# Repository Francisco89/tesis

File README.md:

tesis
=====

El repositorio de mi tesis.

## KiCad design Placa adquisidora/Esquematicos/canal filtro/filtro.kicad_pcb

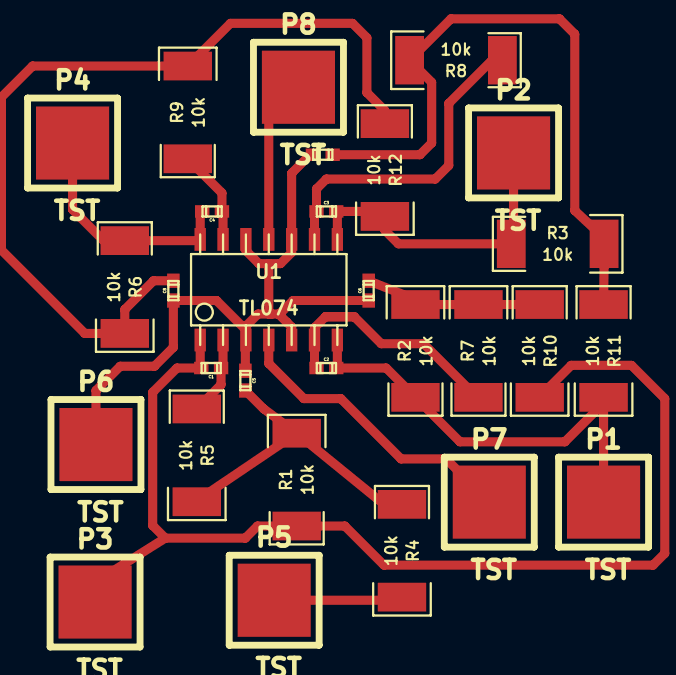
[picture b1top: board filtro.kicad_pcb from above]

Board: 2 copper layers, 29 parts (0 on the bottom side), 16 nets.

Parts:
C1: 412pF; c_0402
C2: 357pF; c_0402
C3: 237pF; c_0402
C4: 82.5pF; c_0402
C5: 976pF; c_0402
C6: 1.15nF; c_0402
C7: 1.74nF; c_0402
C8: 4.87nF; c_0402
P1, P2, P3, P4, P5, P6, P7, P8: TST; 1PIN_SMD
R1, R2, R3, R4, R5, R6, R7, R8, R9, R10, R11, R12: 10k; r_2010
U1: TL074; so-14

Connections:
AGND: C5.2, C6.2, C7.2, C8.2, P6.1, U1.3, U1.5, U1.10, U1.12
unnamed: C1.2, R5.2, U1.2
unnamed: C2.2, R7.2, U1.6
unnamed: C3.1, P2.1, R3.2, R12.1, U1.8
unnamed: C4.2, R9.2, U1.13
unnamed: C1.1, P3.1, R1.2, R10.1, U1.1
unnamed: C2.1, P1.1, R2.2, R11.1, U1.7
unnamed: C3.2, R8.2, U1.9
unnamed: C7.1, R3.1, R8.1, R11.2
unnamed: C8.1, R6.1, R9.1, R12.2
unnamed: C5.1, R1.1, R4.2, R5.1
unnamed: C6.1, R2.1, R7.1, R10.2
unnamed: P5.1, R4.1
unnamed: C4.1, P4.1, R6.2, U1.14
VCC: P7.1, U1.4
VSS: P8.1, U1.11

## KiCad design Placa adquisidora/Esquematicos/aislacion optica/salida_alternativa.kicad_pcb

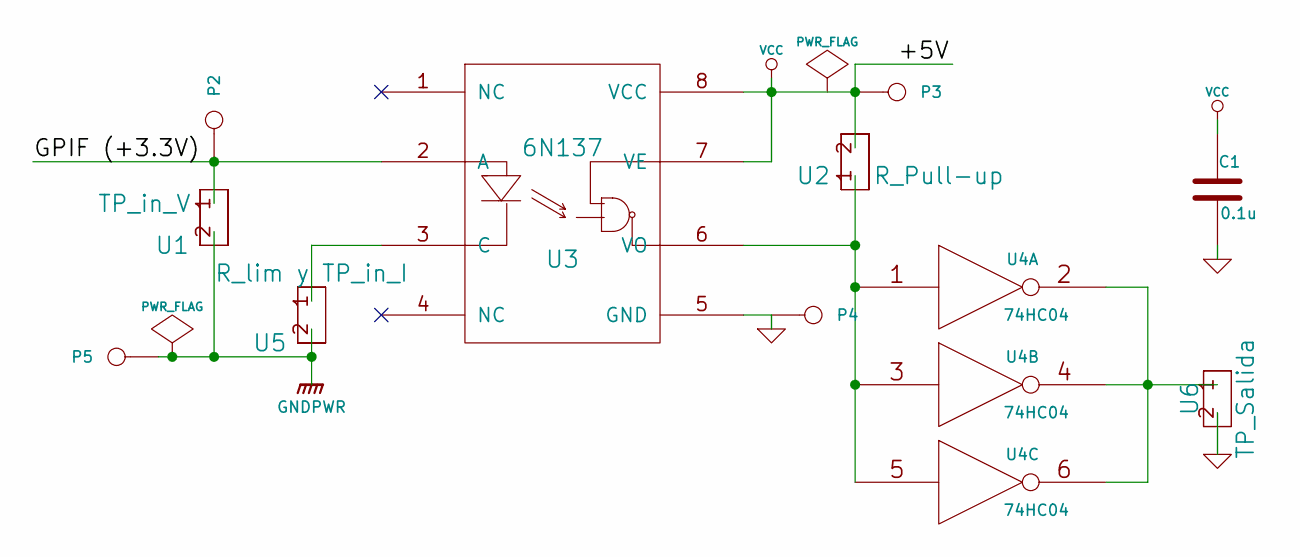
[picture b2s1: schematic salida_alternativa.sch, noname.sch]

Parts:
C1: 0.1u
P2, P3, P4, P5: CONN_1
U1: TP_in_V
U2: R_Pull-up
U3: 6N137
U4: 74HC04
U5: R_lim y TP_in_I
U6: TP_Salida

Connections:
/GPIF (+3.3V): P2.1, U1.1, U3.2 (A)
GND: C1.2, P4.1, U3.5 (GND), U4.7 (GND), U6.2
GNDPWR: P5.1, U1.2, U5.2
unnamed: U3.3 (C), U5.1
unnamed: U4.2, U4.4, U4.6, U6.1
unnamed: U2.1, U3.6 (VO), U4.1, U4.3, U4.5
VCC: C1.1, P3.1, U2.2, U3.7 (VE), U3.8 (VCC), U4.14 (VCC)

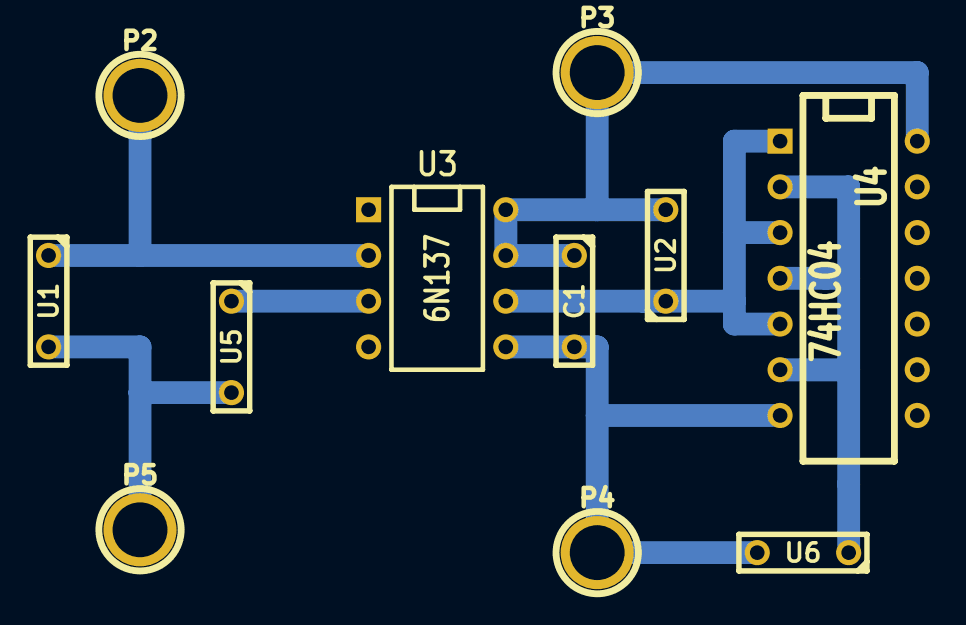
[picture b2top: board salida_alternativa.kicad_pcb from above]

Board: 2 copper layers, 11 parts (0 on the bottom side), 7 nets.

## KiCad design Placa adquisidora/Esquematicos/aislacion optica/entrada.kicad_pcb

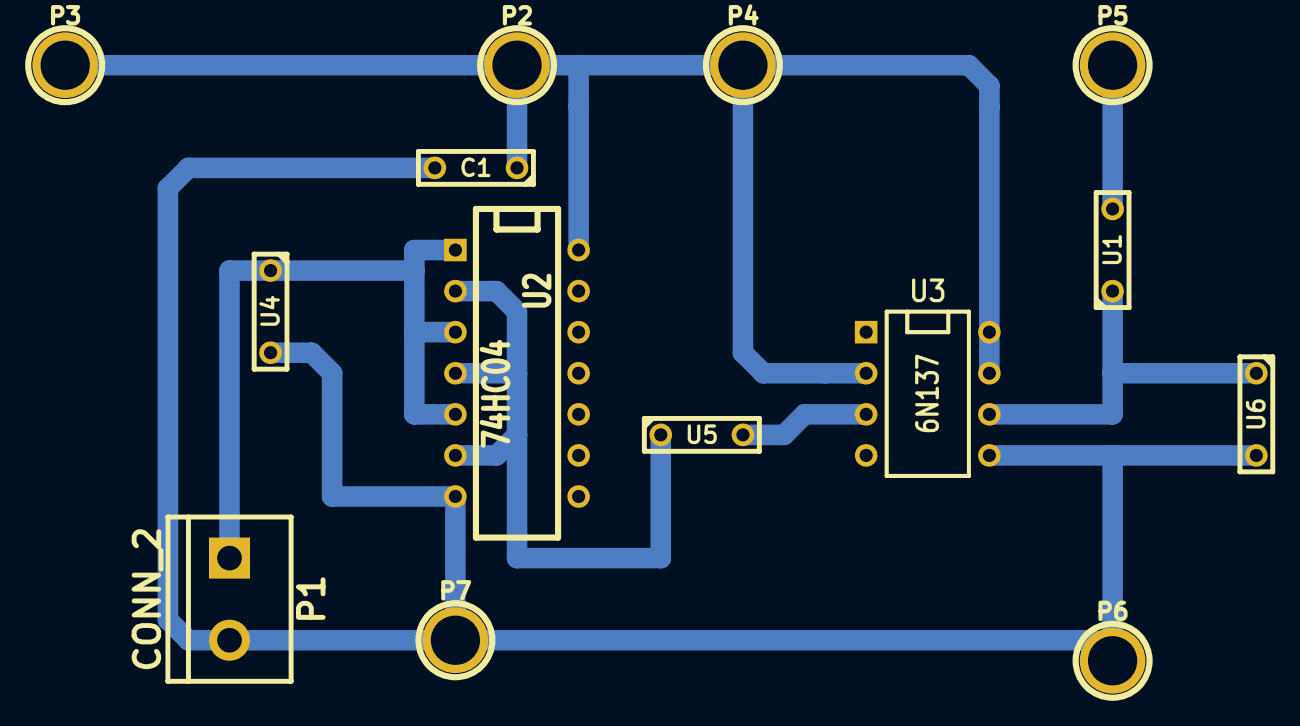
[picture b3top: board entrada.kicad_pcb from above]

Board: 2 copper layers, 14 parts (0 on the bottom side), 7 nets.

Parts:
C1: 0.1u; C2
P1: CONN_2; bornier2
P2, P3, P4, P5, P6, P7: CONN_1; 1pin
U1: R_pull-up; C2
U2: 74HC04; DIP-14__300
U3: 6N137; DIP-8__300
U4: TP_entrada; C2
U5: R_limitadora; C2
U6: TP_salida; C2

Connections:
+3.3V: P5.1, U1.2
AGND: C1.2, P1.2, P6.1, P7.1, U2.7, U3.5, U4.2, U6.2
unnamed: U1.1, U3.6, U6.1
unnamed: U2.2, U2.4, U2.6, U5.1
unnamed: P1.1, U2.1, U2.3, U2.5, U4.1
unnamed: U3.3, U5.2
VAA: C1.1, P2.1, P3.1, P4.1, U2.14, U3.2, U3.7, U3.8

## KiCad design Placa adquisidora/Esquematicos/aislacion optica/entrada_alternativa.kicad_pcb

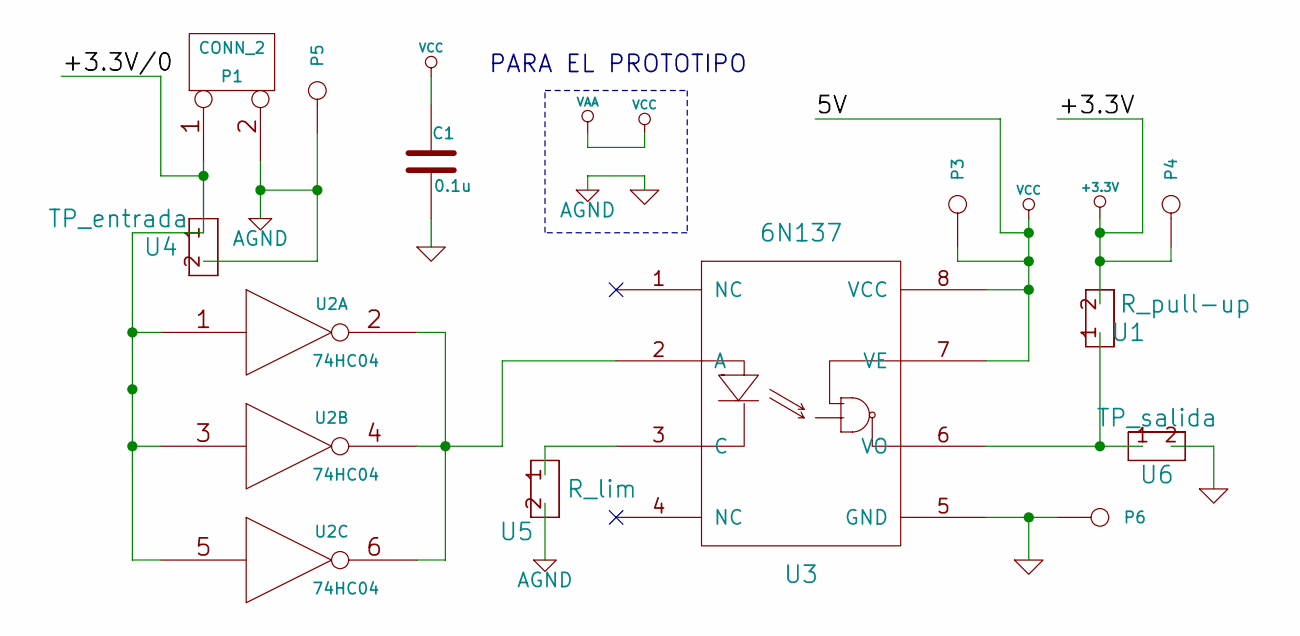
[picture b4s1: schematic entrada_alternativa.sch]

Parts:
C1: 0.1u
P1: CONN_2
P3, P4, P5, P6: CONN_1
U1: R_pull-up
U2: 74HC04
U3: 6N137
U4: TP_entrada
U5: R_lim
U6: TP_salida

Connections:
+3.3V: P4.1, U1.2
AGND: C1.2, P1.2 (PM), P5.1, P6.1, U2.7 (GND), U3.5 (GND), U4.2, U5.2, U6.2
unnamed: U1.1, U3.6 (VO), U6.1
unnamed: P1.1, U2.1, U2.3, U2.5, U4.1
unnamed: U2.2, U2.4, U2.6, U3.2 (A)
unnamed: U3.3 (C), U5.1
VAA: C1.1, P3.1, U2.14 (VCC), U3.7 (VE), U3.8 (VCC)

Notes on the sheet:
PARA EL PROTOTIPO

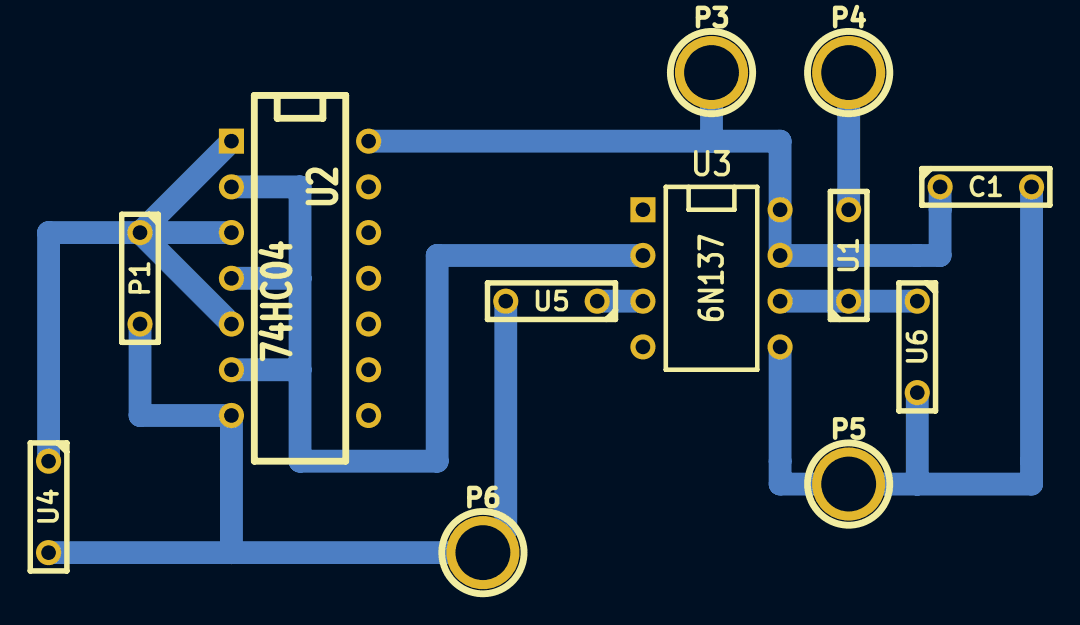
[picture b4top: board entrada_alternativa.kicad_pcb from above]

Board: 2 copper layers, 12 parts (0 on the bottom side), 7 nets.

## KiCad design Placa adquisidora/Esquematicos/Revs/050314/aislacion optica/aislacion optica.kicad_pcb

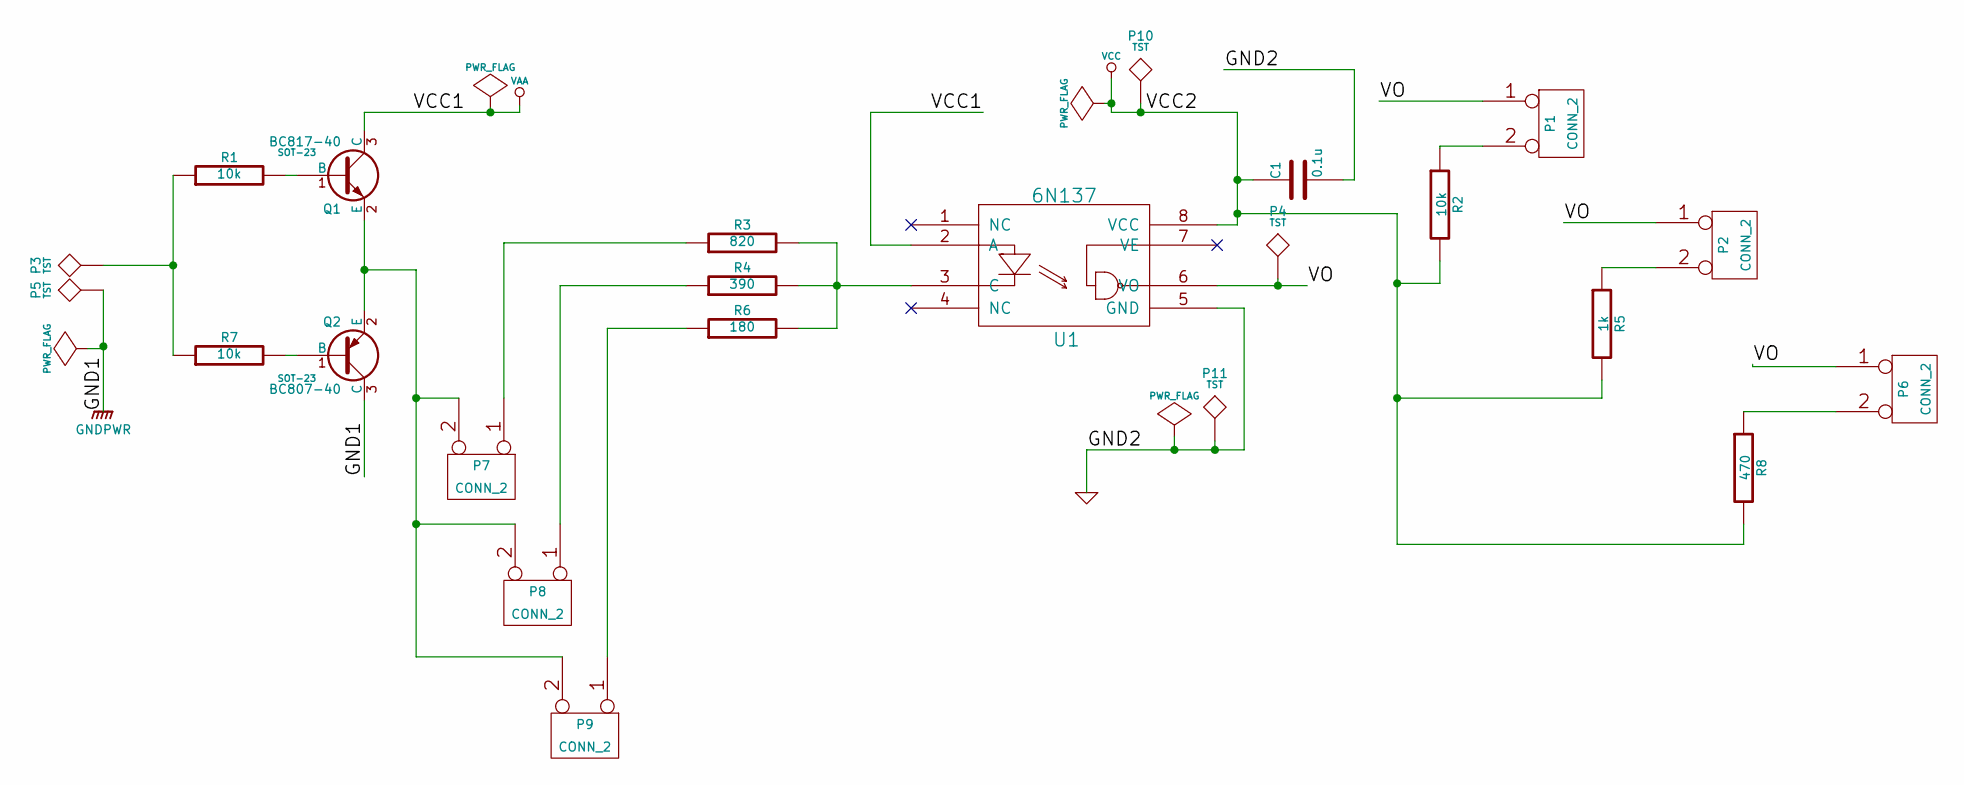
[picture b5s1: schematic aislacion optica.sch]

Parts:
C1: 0.1u
P1, P2, P6, P7, P8, P9: CONN_2
P3, P4, P5, P10, P11: TST
Q1: BC817-40; SOT-23
Q2: BC807-40; SOT-23
R1, R2, R7: 10k
R3: 820
R4: 390
R5: 1k
R6: 180
R8: 470
U1: 6N137

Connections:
/VO: P1.1, P2.1, P4.1, P6.1, U1.6 (VO)
GND: C1.2, P11.1, U1.5 (GND)
GNDPWR: P5.1, Q2.3 (C)
unnamed: Q2.1 (B), R7.2
unnamed: P3.1, R1.1, R7.1
unnamed: Q1.1 (B), R1.2
unnamed: P6.2 (PM), R8.1
unnamed: P2.2 (PM), R5.1
unnamed: P1.2 (PM), R2.1
unnamed: P7.2 (PM), P8.2 (PM), P9.2 (PM), Q1.2 (E), Q2.2 (E)
unnamed: P8.1, R4.1
unnamed: P7.1, R3.1
unnamed: P9.1, R6.1
unnamed: R3.2, R4.2, R6.2, U1.3 (C)
VAA: Q1.3 (C), U1.2 (A)
VCC: C1.1, P10.1, R2.2, R5.2, R8.2, U1.8 (VCC)

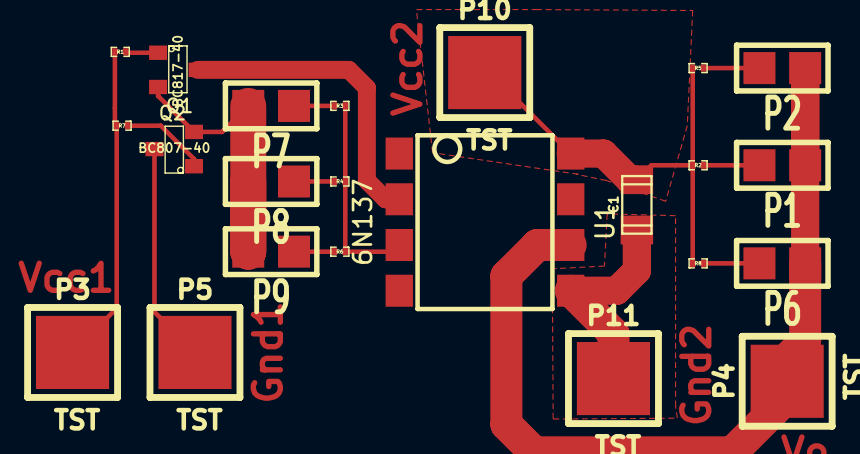
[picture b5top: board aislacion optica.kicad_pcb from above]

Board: 2 copper layers, 23 parts (0 on the bottom side), 16 nets.

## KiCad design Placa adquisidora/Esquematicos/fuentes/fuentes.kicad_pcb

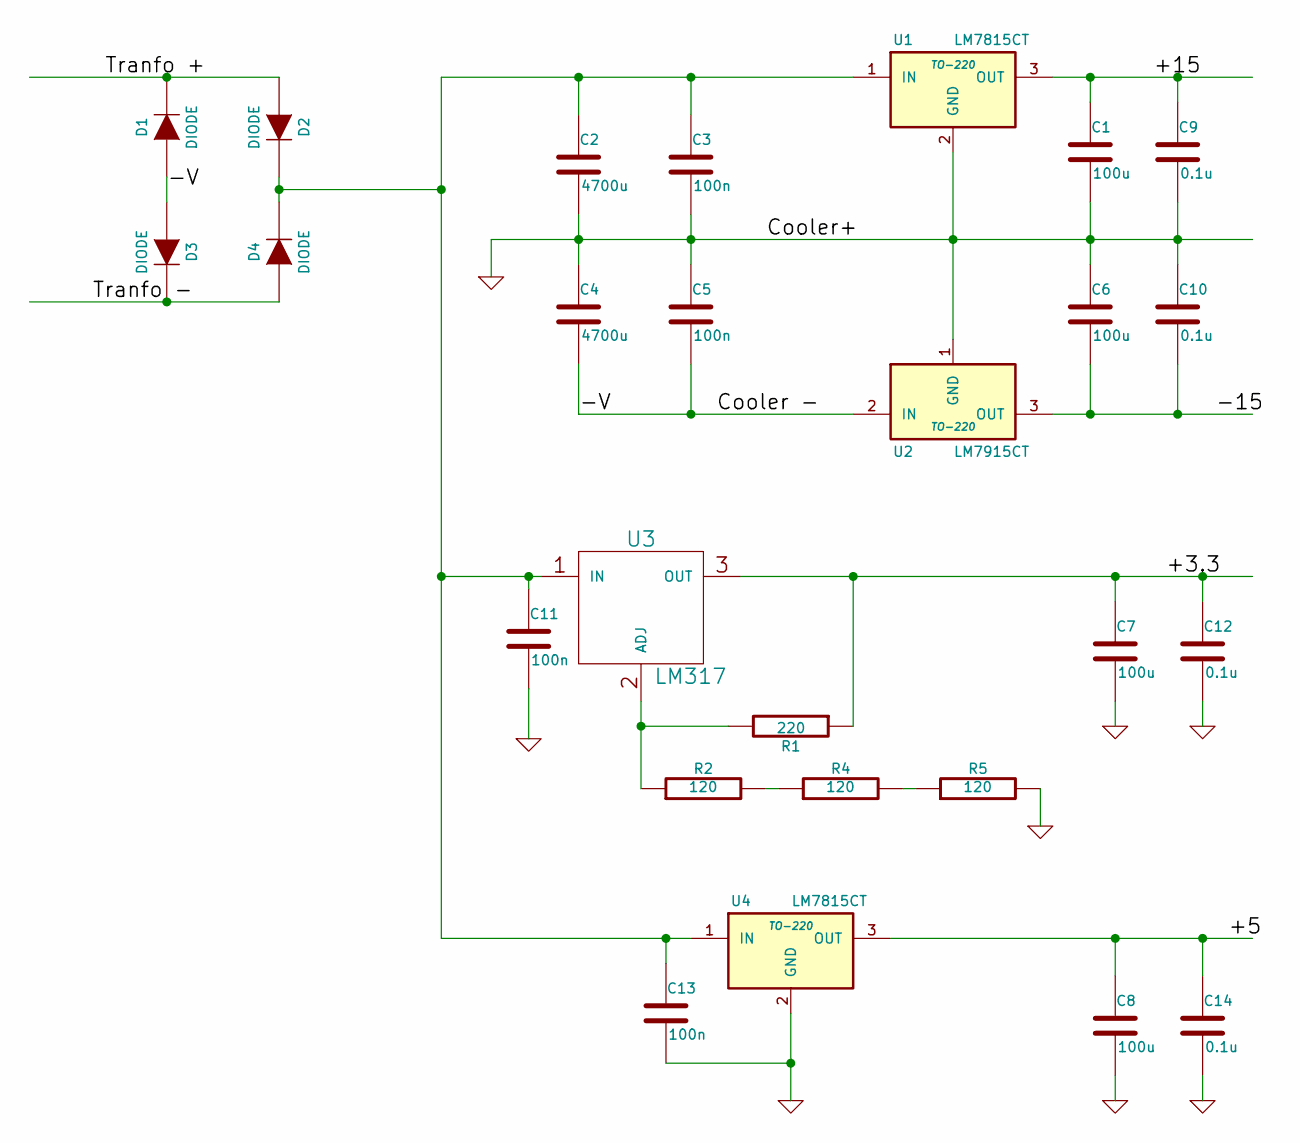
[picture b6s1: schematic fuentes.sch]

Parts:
C1, C6, C7, C8: 100u
C2, C4: 4700u
C3, C5, C11, C13: 100n
C9, C10, C12, C14: 0.1u
D1, D2, D3, D4: DIODE
R1: 220
R2, R4, R5: 120
U1, U4: LM7815CT; TO-220
U2: LM7915CT; TO-220
U3: LM317

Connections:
/+3.3: C7.1, C12.1, R1.1, U3.3 (OUT)
/+5: C8.1, C14.1, U4.3 (OUT)
/+15: C1.1, C9.1, U1.3 (OUT)
/-15: C6.2, C10.2, U2.3 (OUT)
/-V: C4.2, C5.2, D1.1 (A), D3.1 (A), U2.2 (IN)
/Tranfo +: D1.2 (K), D2.1 (A)
/Tranfo -: D3.2 (K), D4.1 (A)
GND: C1.2, C2.2, C3.2, C4.1, C5.1, C6.1, C7.2, C8.2, C9.2, C10.1, C11.2, C12.2, C13.2, C14.2, R5.2, U1.2 (GND), U2.1 (GND), U4.2 (GND)
unnamed: C2.1, C3.1, C11.1, C13.1, D2.2 (K), D4.2 (K), U1.1 (IN), U3.1 (IN), U4.1 (IN)
unnamed: R2.2, R4.1
unnamed: R1.2, R2.1, U3.2 (ADJ)
unnamed: R4.2, R5.1

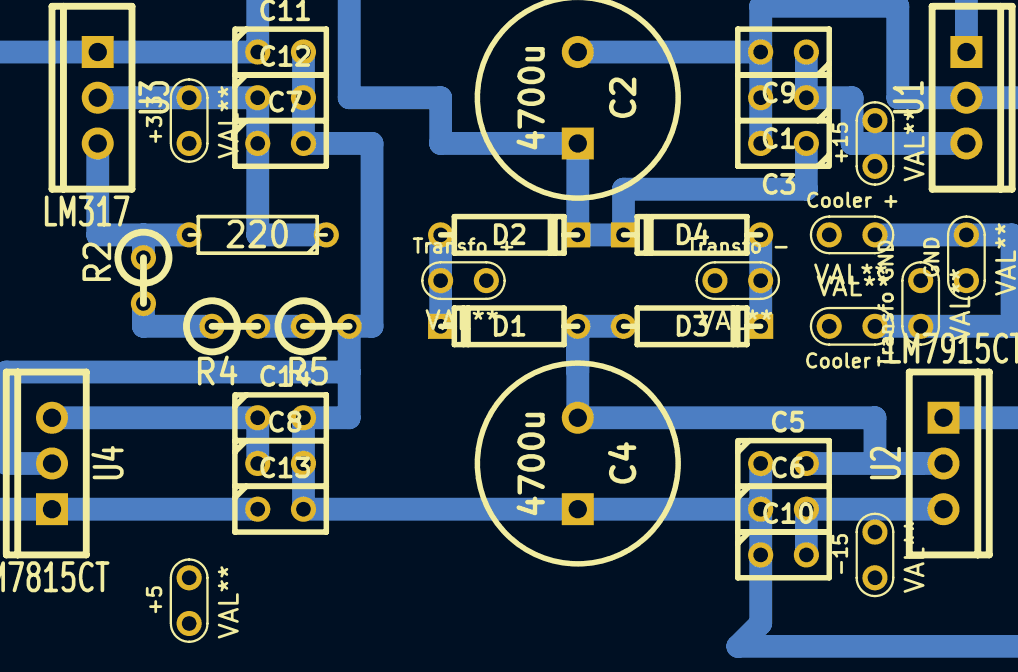
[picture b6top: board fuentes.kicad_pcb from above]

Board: 2 copper layers, 36 parts (0 on the bottom side), 12 nets.

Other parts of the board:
+3.3, +5, +15: VAL**; TEST_POINT_2PADS
-15: VAL**; TEST_POINT_2PADS
Cooler +: VAL**; TEST_POINT_2PADS
Cooler -: VAL**; TEST_POINT_2PADS
GND: VAL**; TEST_POINT_2PADS
Transfo +: VAL**; TEST_POINT_2PADS
Transfo -: VAL**; TEST_POINT_2PADS
Transfo GND: VAL**; TEST_POINT_2PADS

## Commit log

2013-09-10 probando
2013-09-10 borre el readme
2013-09-17 Hola
2013-09-18 Copie el proyecto de la compu de Ricardo, lo recompile en esta compu y escribi el tutorial sobre como lo hicimos.
2013-09-23 Primera parte del streamer, puedo leer endpoints con el sourcesink en mi streamer casero. Falta mejorar la programacion, poner headers y sacar cosas del main
2013-09-23 Leer mensaje de recien
2013-09-24 24 del 9, fui a ver a Haykin, estoy tratando de agregar la funcion del loopback al programa.
2013-09-24 Puedo escribir el endpoint pero no puedo leer con XferData
2013-09-25 Guardo una version del streamer que escribe un endpoint OUT y lee un endpoint IN que funciona HOY
2013-10-07 Agrego las cosas que borre
2013-10-07 entra todo
2013-10-15 Agrego dos tutoriales en txt, PWM y PPort. Agrego tambien el firmware y creo que las maquinas de estado que usan en la carpeta workspace eclipse.
2013-10-16 el proyecto de Qt usb2gpio ahora efectivamente crea un PWM y lo escribe en el endpoint de salida identificado en el codigo, el cual se puede cambiar a gusto.
2013-10-29 Automaster (eclipse) y usb2gpio (qt) actualizados. Es un streamning al puerto GPIF II por USB que prende 16 bits (prende 16, no LOS 16 que dice la placa pero hay 16). El automaster es un master FIFO 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
2013-10-30 Lo que hice hoy: probe que la maquina puede mandar un LONG con su numero maximo cada 1us, sacando en pantalla cada 1s. Paso siguiente, ver si puede hacer un loopback con un DMA automatico de un endpo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
2013-11-07 Tal y como sospechaba, el buffer del usb se drena de a 16 bit (u 8, 24 o 32, a gusto del consumidor) al puerto USB. Por ende escribi un patron distinto y se va imprimiendo cada 16 bits al puerto usb.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
2014-01-17 agrego la carpeta placa adquisidora
2014-01-17 agrego los bloques y los componentes elegidos hasta ahora
2014-04-21 Actualizacion GIT 21 04 14 salvar archivos
